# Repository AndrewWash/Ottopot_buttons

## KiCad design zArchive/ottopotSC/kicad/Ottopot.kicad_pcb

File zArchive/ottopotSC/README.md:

# ottopot MIDI Controller
Version 1.1
License: GPL v3 (http://www.gnu.org/licenses/gpl.html)
https://gerotakke.de/ottopot

The ottopot is a MIDI controller with 8 endless potentiometers. It sends 14bit CCs and tries to mimic the feel of
“regular analog potentiometers” as good as possible. It uses Duppa's small LED rings to indicate the current value
of each pot (optional). MIDI feedback is supported so changes of the digital value in the DAW will be reflected by the LEDS.
It's aimed to control Bitwig's Remote Controls or Logic's Smart Controls.

The case is fully 3D printed, Blender files are in this repo and print files are on printables.com.
Build guide and material lists are on https://gerotakke.de/ottopot

### Build

If you want to just update to the newest version, download [the current firmware.hex file](https://codeberg.org/gerotakke/ottopot/releases) and flash it to the Teensy using [tytools](https://github.com/Koromix/tytools) TyUploader.

The code is a [platformIO](https://platformio.org/){target="_blank"} project. I'm using platformIO core from the command line but
the VSCode extension should be fine as well.  
Clone the [project from the repo](https://codeberg.org/gerotakke/ottopot){target="_blank"} to your computer.  
If you have platformIO set up, make sure you connect the Teensy to your computer via USB and be sure that it is the only Teensy that is connected. Then run `pio run --target upload` from the main directory of the repo and that should be it.  

For Linux users, I've found that only [tytools](https://github.com/Koromix/tytools) can flash the Teensy without having to press the reset button
on the board. I have a commented region in `platformio.ini` with the settings for that.  
It also seems to be the best way to handle flashing when you have multiple Teensys connected.

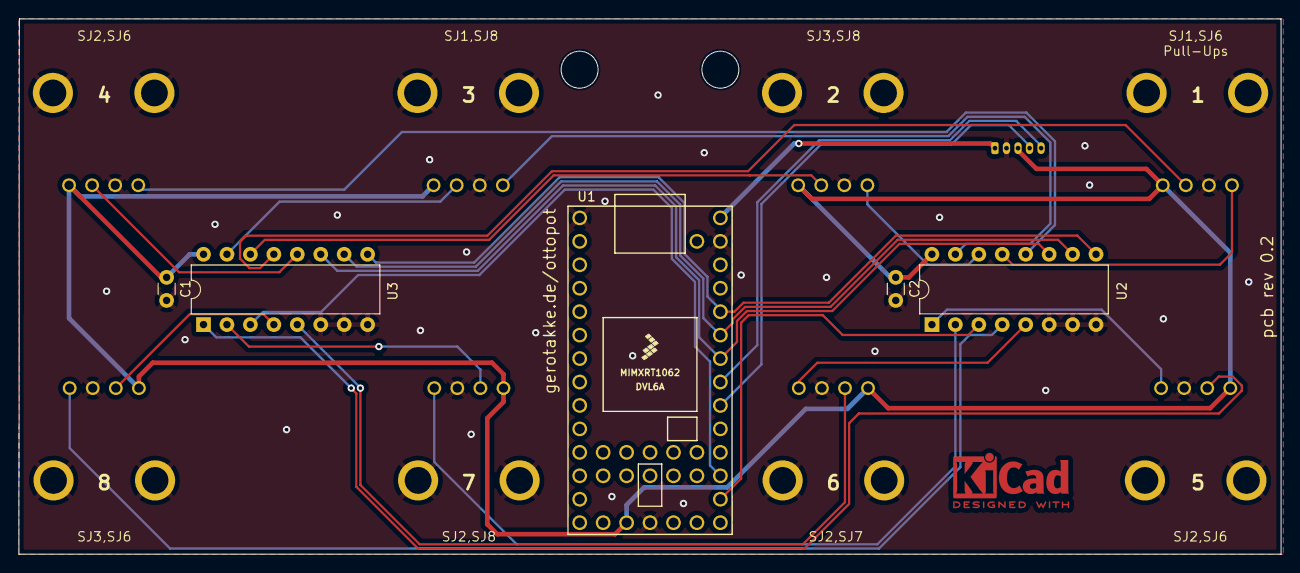
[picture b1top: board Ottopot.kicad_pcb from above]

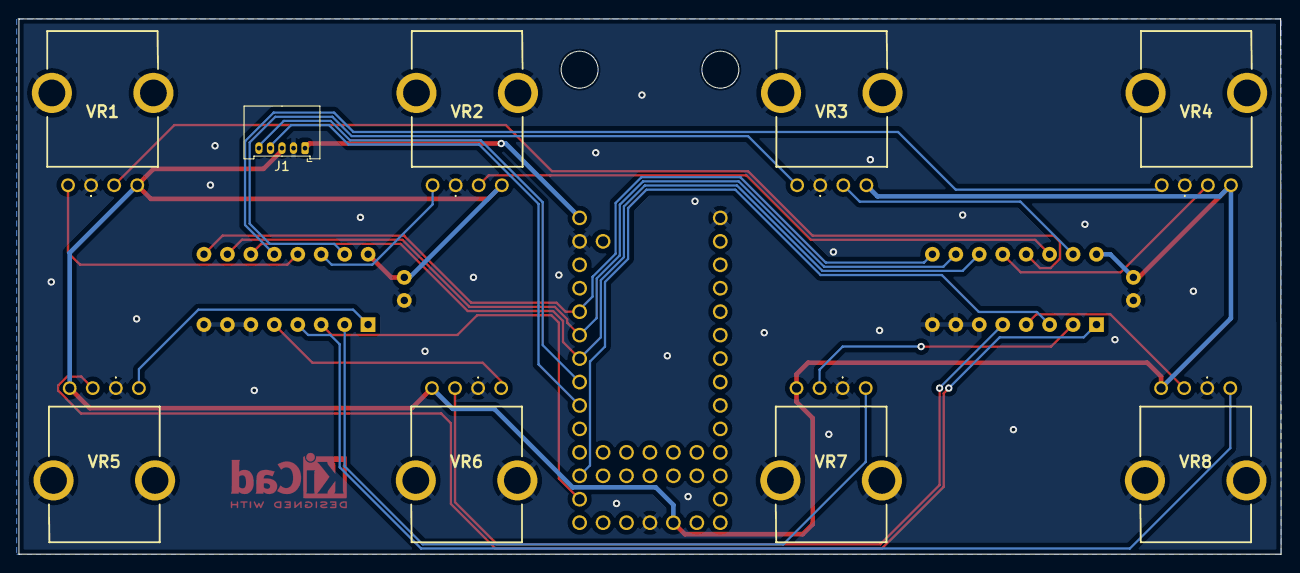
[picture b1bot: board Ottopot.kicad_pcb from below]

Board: 2 copper layers, 136.8 x 58.0 mm, 14 parts (9 on the bottom side), 26 nets.

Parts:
C1, C2: 0.1uF; C_Disc_D3.0mm_W1.6mm_P2.50mm
J1: Conn_01x05; Molex_PicoBlade_53048-0510_1x05_P1.25mm_Horizontal
U1: Teensy4.0; Teensy40
U2, U3: 74HC4051; DIP-16_W7.62mm
VR1, VR2, VR3, VR4, VR5, VR6, VR7, VR8: RV112FF-40B1-15F; RV112FF40B115F

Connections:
+5V: J1.1, U1.33 (VIN)
/S0: U1.27 (20_A6_TX5_LRCLK1), U2.11 (S0), U3.11 (S0)
/S1: U1.28 (21_A7_RX5_BCLK1), U2.10 (S1), U3.10 (S1)
/S2: U1.29 (22_A8_CTX1), U2.9 (S2), U3.9 (S2)
/SCL: J1.5, U1.26 (19_A5_SCL0)
/SDA: J1.4, U1.25 (18_A4_SDA0)
/w1_1: U2.13 (A0), VR1.A2 (WIPER_1)
/w1_2: U3.13 (A0), VR1.B2 (WIPER_2)
/w2_1: U2.14 (A1), VR2.A2 (WIPER_1)
/w2_2: U3.14 (A1), VR2.B2 (WIPER_2)
/w3_1: U2.15 (A2), VR3.A2 (WIPER_1)
/w3_2: U3.15 (A2), VR3.B2 (WIPER_2)
/w4_1: U2.12 (A3), VR4.A2 (WIPER_1)
/w4_2: U3.12 (A3), VR4.B2 (WIPER_2)
/w5_1: U2.1 (A4), VR5.A2 (WIPER_1)
/w5_2: U3.1 (A4), VR5.B2 (WIPER_2)
/w6_1: U2.5 (A5), VR6.A2 (WIPER_1)
/w6_2: U3.5 (A5), VR6.B2 (WIPER_2)
/w7_1: U2.2 (A6), VR7.A2 (WIPER_1)
/w7_2: U3.2 (A6), VR7.B2 (WIPER_2)
/w8_1: U2.4 (A7), VR8.A2 (WIPER_1)
/w8_2: U3.4 (A7), VR8.B2 (WIPER_2)
GND: C1.2, C2.2, J1.2, U1.1 (GND), U1.17 (GND), U1.32 (GND), U2.6 (~E), U2.7 (VEE), U2.8 (GND), U3.6 (~E), U3.7 (VEE), U3.8 (GND), VR1.A1 (CCW), VR1.MH1, VR1.MH2, VR2.A1 (CCW), VR2.MH1, VR2.MH2, VR3.A1 (CCW), VR3.MH1, VR3.MH2, VR4.A1 (CCW), VR4.MH1, VR4.MH2, VR5.A1 (CCW), VR5.MH1, VR5.MH2, VR6.A1 (CCW), VR6.MH1, VR6.MH2, VR7.A1 (CCW), VR7.MH1, VR7.MH2, VR8.A1 (CCW), VR8.MH1, VR8.MH2
unnamed: U1.21 (14_A0_TX3_SPDIF_OUT), U2.3 (A)
unnamed: U1.22 (15_A1_RX3_SPDIF_IN), U3.3 (A)
VCC: C1.1, C2.1, J1.3, U1.16 (3V3), U2.16 (VCC), U3.16 (VCC), VR1.A3 (CW), VR2.A3 (CW), VR3.A3 (CW), VR4.A3 (CW), VR5.A3 (CW), VR6.A3 (CW), VR7.A3 (CW), VR8.A3 (CW)

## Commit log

2026-05-15 Initial commit - Worked off of github initially. Should be pretty close but need to wire it up and compile firmware to test
2026-05-15 code review findings
2026-05-16 prelim fixes. Seems to fix the "resume from last knob postiton" issue as well!
2026-05-16 first attempt at fixing the lagout at slow speeds. seems a bit better...
2026-05-16 forgot this
2026-05-16 this is about a 90% solution. I could live with this and it is deff an improvement for sure. gonna keep going tho.
2026-05-16 ULTRA RESPONSIVE but writes ghost values plus minus .2 randomly in bitwig. need to dial in
2026-05-16 version 1.0 done. ottopot_fine_fix.ino.hex lets get it
2026-05-16 New method prelim build. seems to be better with the random value throwing, maybe tweak more.
2026-05-16 New method prelim build. seems to be better with the random value throwing, maybe tweak more. backup just in case
2026-05-16 V2 DONE - 100 percent working no random midi values writing

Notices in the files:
zArchive/ottopotSC/kicad/Ottopot.kicad_pcb:
License: CC BY 4.0
